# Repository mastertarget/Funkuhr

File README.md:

# Funkuhr
I needed a radio controlled diy clock, so i developed a PCB as
mainboard for this clock.
It's based on an Arduino UNO which controlles four 74HC654
octal-latches with ULN2004 darlington transistor arrays which
drives 4 self made seven segment displays.

http://ncdf.de/?p=81

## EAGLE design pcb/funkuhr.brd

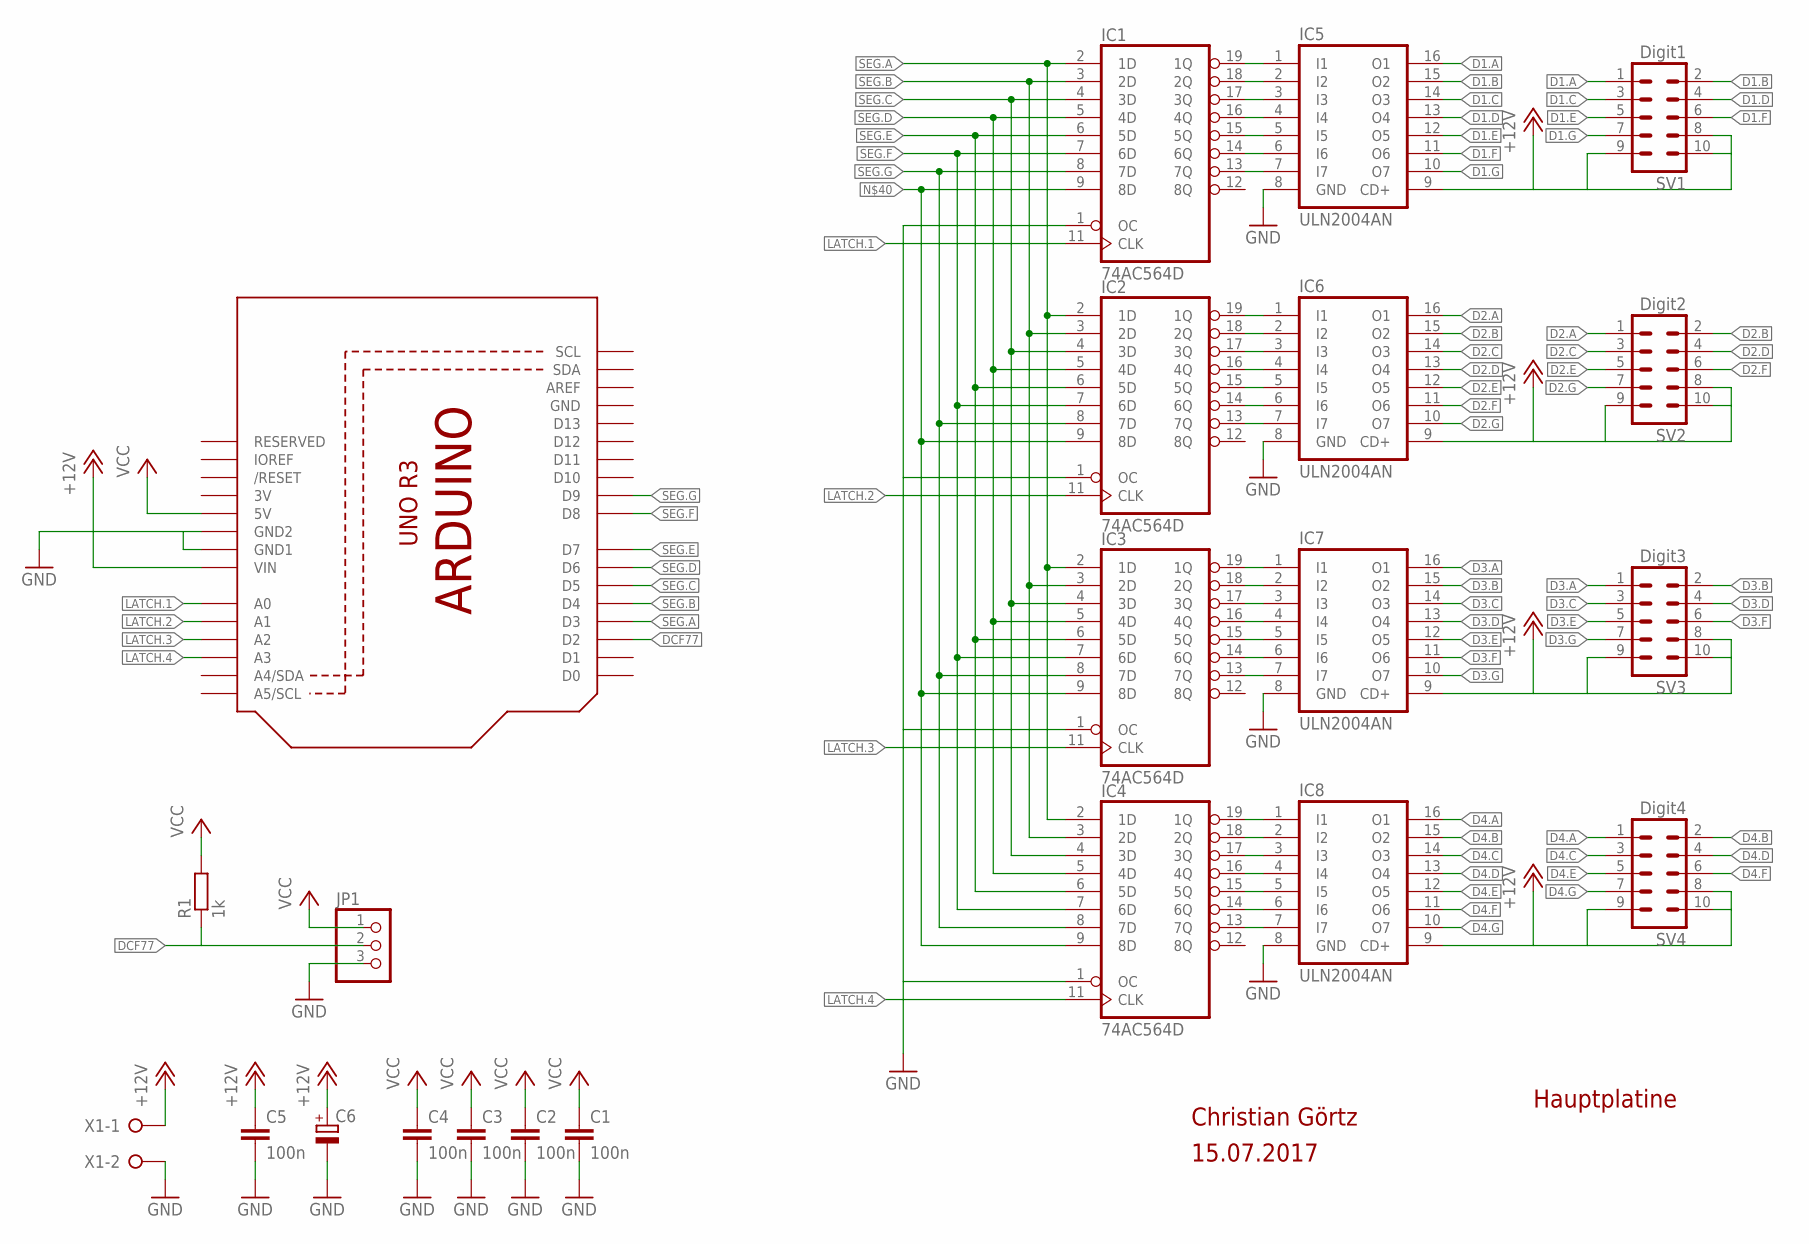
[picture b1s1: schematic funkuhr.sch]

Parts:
C1, C2, C3, C4: 100n; C0805
C5: 100n; C050-024X044
C6: CPOL-EUE2.5-6; E2,5-6
IC1, IC2, IC3, IC4: 74AC564D; SO20W
IC5, IC6, IC7, IC8: ULN2004AN; DIL16
JP1: PINHD-1X3; 1X03
R1: 1k; 0207/10
SV1: Digit1; ML10
SV2: Digit2; ML10
SV3: Digit3; ML10
SV4: Digit4; ML10
U1: ARDUINOR3-DIMENSION; ARDUINOR3
X1: W237-02P; W237-132

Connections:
3V: U1.3V
+12V: C5.1, C6.+, IC5.9 (CD+), IC6.9 (CD+), IC7.9 (CD+), IC8.9 (CD+), SV1.8, SV1.9, SV1.10, SV2.8, SV2.9, SV2.10, SV3.8, SV3.9, SV3.10, SV4.8, SV4.9, SV4.10, U1.VIN, X1.1
D1.A: IC5.16 (O1), SV1.1
D1.B: IC5.15 (O2), SV1.2
D1.C: IC5.14 (O3), SV1.3
D1.D: IC5.13 (O4), SV1.4
D1.E: IC5.12 (O5), SV1.5
D1.F: IC5.11 (O6), SV1.6
D1.G: IC5.10 (O7), SV1.7
D2.A: IC6.16 (O1), SV2.1
D2.B: IC6.15 (O2), SV2.2
D2.C: IC6.14 (O3), SV2.3
D2.D: IC6.13 (O4), SV2.4
D2.E: IC6.12 (O5), SV2.5
D2.F: IC6.11 (O6), SV2.6
D2.G: IC6.10 (O7), SV2.7
D3.A: IC7.16 (O1), SV3.1
D3.B: IC7.15 (O2), SV3.2
D3.C: IC7.14 (O3), SV3.3
D3.D: IC7.13 (O4), SV3.4
D3.E: IC7.12 (O5), SV3.5
D3.F: IC7.11 (O6), SV3.6
D3.G: IC7.10 (O7), SV3.7
D4.A: IC8.16 (O1), SV4.1
D4.B: IC8.15 (O2), SV4.2
D4.C: IC8.14 (O3), SV4.3
D4.D: IC8.13 (O4), SV4.4
D4.E: IC8.12 (O5), SV4.5
D4.F: IC8.11 (O6), SV4.6
D4.G: IC8.10 (O7), SV4.7
DCF77: JP1.2, R1.1, U1.D2
GND: C1.2, C2.2, C3.2, C4.2, C5.2, C6.-, IC1.1 (OC), IC1.10 (GND), IC2.1 (OC), IC2.10 (GND), IC3.1 (OC), IC3.10 (GND), IC4.1 (OC), IC4.10 (GND), IC5.8 (GND), IC6.8 (GND), IC7.8 (GND), IC8.8 (GND), JP1.3, U1.GND, U1.GND1, U1.GND2, X1.2
LATCH.1: IC1.11 (CLK), U1.A0
LATCH.2: IC2.11 (CLK), U1.A1
LATCH.3: IC3.11 (CLK), U1.A2
LATCH.4: IC4.11 (CLK), U1.A3
unnamed: IC1.19 (1Q), IC5.1 (I1)
unnamed: IC1.18 (2Q), IC5.2 (I2)
unnamed: IC1.17 (3Q), IC5.3 (I3)
unnamed: IC1.16 (4Q), IC5.4 (I4)
unnamed: IC1.15 (5Q), IC5.5 (I5)
unnamed: IC1.14 (6Q), IC5.6 (I6)
unnamed: IC1.13 (7Q), IC5.7 (I7)
unnamed: IC2.19 (1Q), IC6.1 (I1)
unnamed: IC2.18 (2Q), IC6.2 (I2)
unnamed: IC2.17 (3Q), IC6.3 (I3)
unnamed: IC2.16 (4Q), IC6.4 (I4)
unnamed: IC2.15 (5Q), IC6.5 (I5)
unnamed: IC2.14 (6Q), IC6.6 (I6)
unnamed: IC2.13 (7Q), IC6.7 (I7)
unnamed: IC3.19 (1Q), IC7.1 (I1)
unnamed: IC3.18 (2Q), IC7.2 (I2)
unnamed: IC3.17 (3Q), IC7.3 (I3)
unnamed: IC3.16 (4Q), IC7.4 (I4)
unnamed: IC3.15 (5Q), IC7.5 (I5)
unnamed: IC3.14 (6Q), IC7.6 (I6)
unnamed: IC3.13 (7Q), IC7.7 (I7)
unnamed: IC4.19 (1Q), IC8.1 (I1)
unnamed: IC4.18 (2Q), IC8.2 (I2)
unnamed: IC4.17 (3Q), IC8.3 (I3)
unnamed: IC4.16 (4Q), IC8.4 (I4)
unnamed: IC4.15 (5Q), IC8.5 (I5)
unnamed: IC4.14 (6Q), IC8.6 (I6)
unnamed: IC4.13 (7Q), IC8.7 (I7)
unnamed: IC1.9 (8D), IC2.9 (8D), IC3.9 (8D), IC4.9 (8D)
SEG.A: IC1.2 (1D), IC2.2 (1D), IC3.2 (1D), IC4.2 (1D), U1.D3
SEG.B: IC1.3 (2D), IC2.3 (2D), IC3.3 (2D), IC4.3 (2D), U1.D4
SEG.C: IC1.4 (3D), IC2.4 (3D), IC3.4 (3D), IC4.4 (3D), U1.D5
SEG.D: IC1.5 (4D), IC2.5 (4D), IC3.5 (4D), IC4.5 (4D), U1.D6
SEG.E: IC1.6 (5D), IC2.6 (5D), IC3.6 (5D), IC4.6 (5D), U1.D7
SEG.F: IC1.7 (6D), IC2.7 (6D), IC3.7 (6D), IC4.7 (6D), U1.D8
SEG.G: IC1.8 (7D), IC2.8 (7D), IC3.8 (7D), IC4.8 (7D), U1.D9
VCC: C1.1, C2.1, C3.1, C4.1, IC1.20 (VCC), IC2.20 (VCC), IC3.20 (VCC), IC4.20 (VCC), JP1.1, R1.2, U1.5V

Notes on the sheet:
Christian Görtz
15.07.2017
Hauptplatine

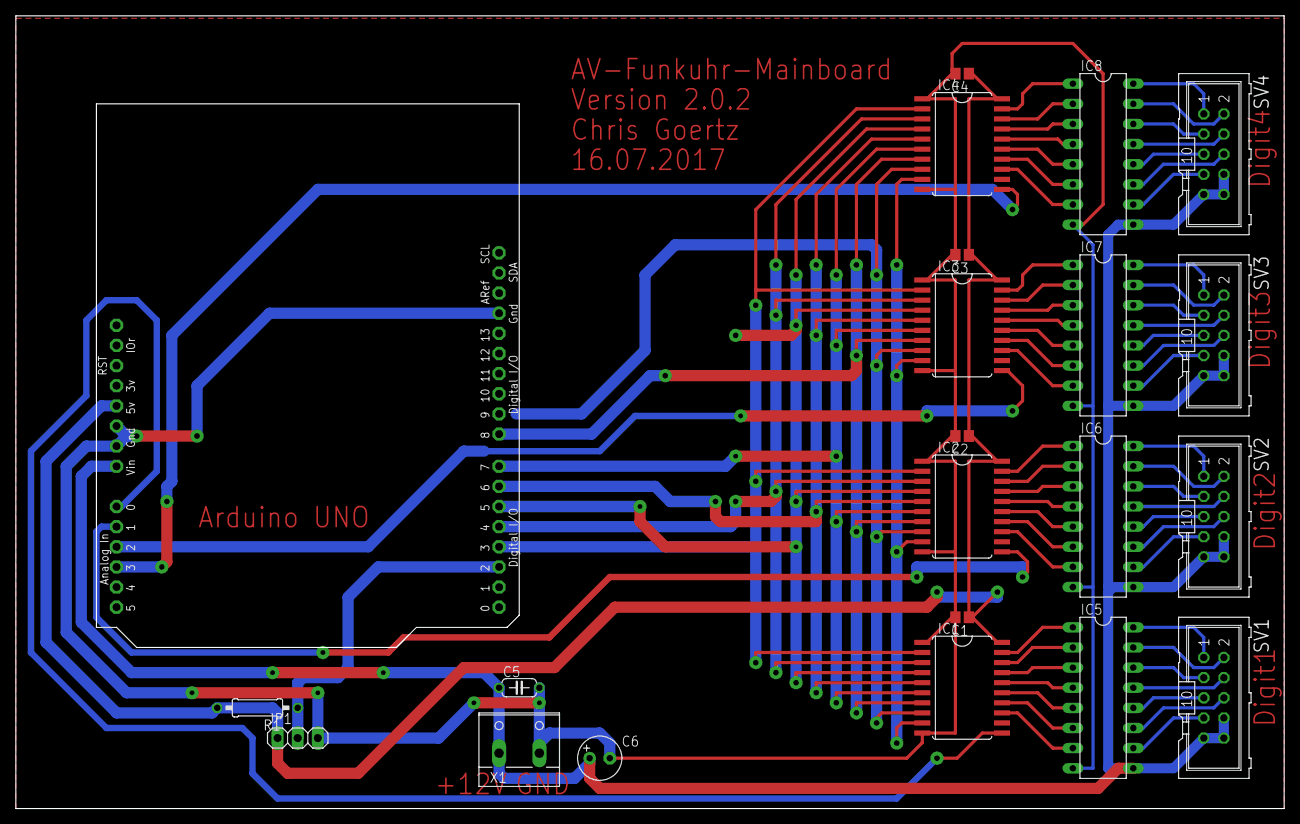
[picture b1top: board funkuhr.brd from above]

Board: 2 copper layers, 160.0 x 100.0 mm, 22 parts (0 on the bottom side), 72 nets.

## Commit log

2017-07-28 LICENSE added
2017-07-28 pcb design files added
2017-07-28 Set theme jekyll-theme-time-machine
